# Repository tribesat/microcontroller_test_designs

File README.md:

# microcontroller_test_designs
Practice designing and manufacturing microcontroller boards

# License Information

The hardware is released under [Creative Commons Share-alike 3.0](http://creativecommons.org/licenses/by-sa/3.0/).  

## ATmega328P_QFP

These desgines are adapted from the [Sparkfun Arduino Pro Mini](https://github.com/sparkfun/Arduino_Pro_Mini_328)

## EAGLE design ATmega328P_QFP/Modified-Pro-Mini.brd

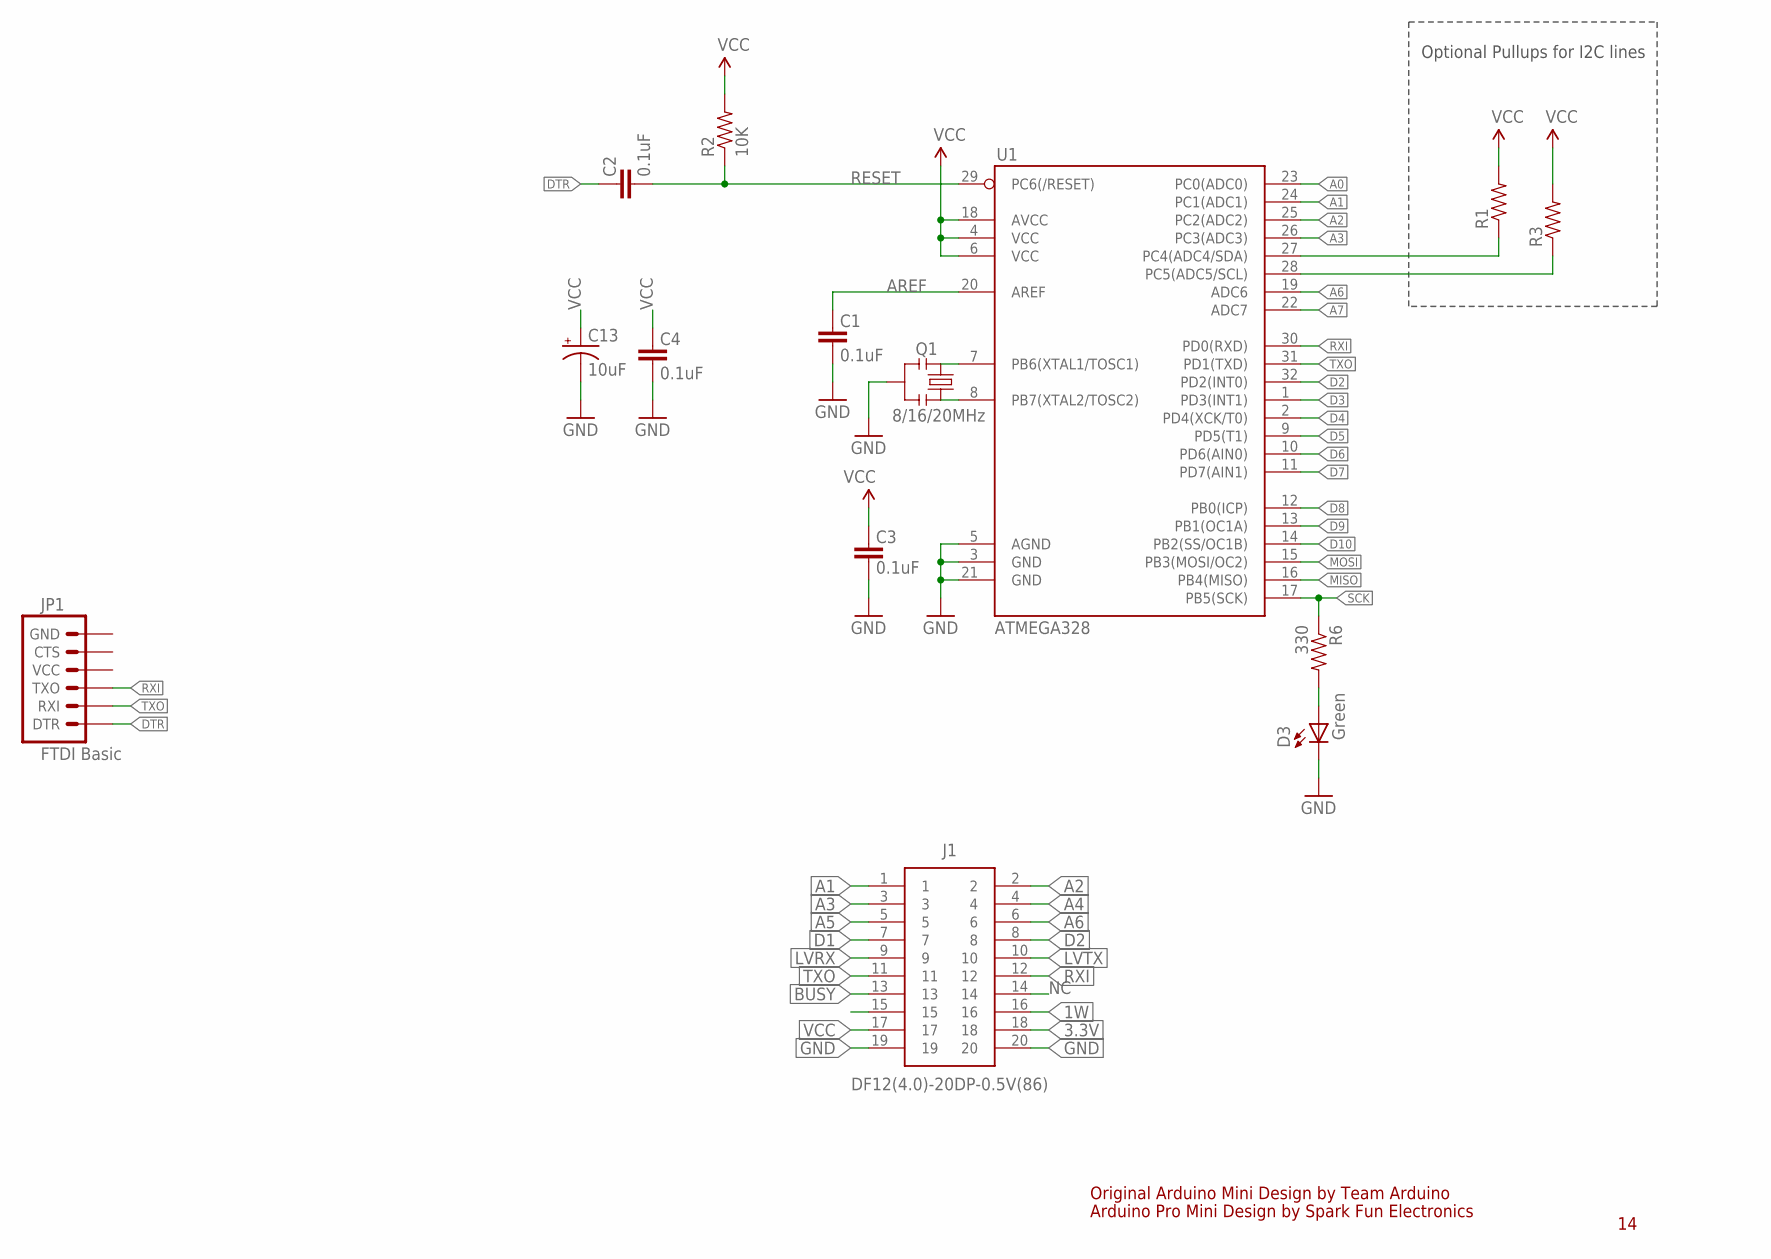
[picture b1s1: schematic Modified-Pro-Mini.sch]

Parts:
C1, C2, C3, C4: 0.1uF; 0603-CAP
C13: 10uF; EIA3216
D3: Green; 0603-LED-ALT1
J1: DF12(4.0)-20DP-0.5V(86); DF12(4.0)-20DP
JP1: FTDI Basic; 1X06
Q1: 8/16/20MHz; RESONATOR-SMD-1:1
R1, R3: RESISTOR0603-RES; 0603-RES
R2: 10K; 0603-RES
R6: 330; 0603-RES
U1: ATMEGA328; TQFP32-08

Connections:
1W: J1.16
3.3V: J1.18
A0: U1.23 (PC0(ADC0))
A1: J1.1, U1.24 (PC1(ADC1))
A2: J1.2, U1.25 (PC2(ADC2))
A3: J1.3, U1.26 (PC3(ADC3))
A4: J1.4, R1.1, U1.27 (PC4(ADC4/SDA))
A5: J1.5, R3.1, U1.28 (PC5(ADC5/SCL))
A6: J1.6, U1.19 (ADC6)
A7: U1.22 (ADC7)
AREF: C1.2, U1.20 (AREF)
BUSY: J1.13
D1: J1.7
D2: J1.8, U1.32 (PD2(INT0))
D3: U1.1 (PD3(INT1))
D4: U1.2 (PD4(XCK/T0))
D5: U1.9 (PD5(T1))
D6: U1.10 (PD6(AIN0))
D7: U1.11 (PD7(AIN1))
D8: U1.12 (PB0(ICP))
D9: U1.13 (PB1(OC1A))
D10: U1.14 (PB2(SS/OC1B))
DTR: C2.2, JP1.1 (DTR)
GND: C1.1, C3.1, C4.1, C13.C (-), D3.C, J1.19, J1.20, Q1.2, U1.3 (GND), U1.5 (AGND), U1.21 (GND)
LVRX: J1.9
LVTX: J1.10
MISO: U1.16 (PB4(MISO))
MOSI: U1.15 (PB3(MOSI/OC2))
unnamed: Q1.3, U1.8 (PB7(XTAL2/TOSC2))
unnamed: Q1.1, U1.7 (PB6(XTAL1/TOSC1))
unnamed: D3.A, R6.2
NC: J1.14
RESET: C2.1, R2.1, U1.29 (PC6(/RESET))
RXI: J1.12, JP1.3 (TXO), U1.30 (PD0(RXD))
SCK: R6.1, U1.17 (PB5(SCK))
TXO: J1.11, JP1.2 (RXI), U1.31 (PD1(TXD))
VCC: C3.2, C4.2, C13.A (+), J1.17, R1.2, R2.2, R3.2, U1.4 (VCC), U1.6 (VCC), U1.18 (AVCC)

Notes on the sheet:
Original Arduino Mini Design by Team Arduino
Arduino Pro Mini Design by Spark Fun Electronics
Optional Pullups for I2C lines

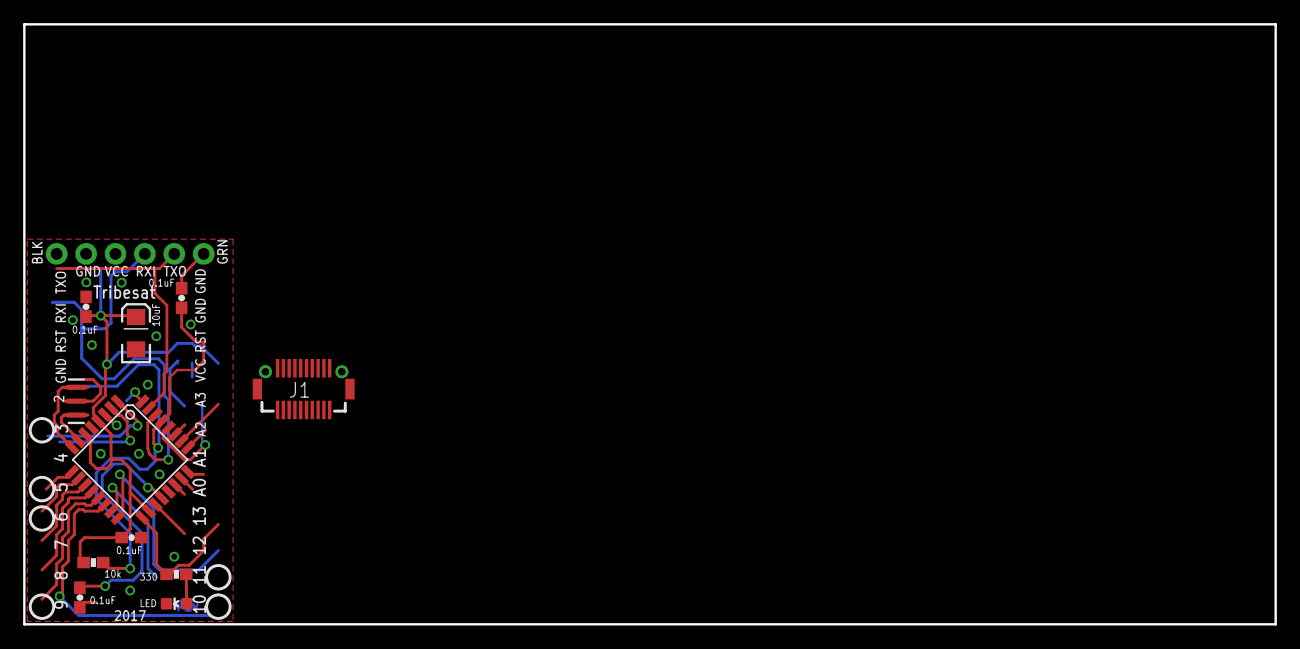
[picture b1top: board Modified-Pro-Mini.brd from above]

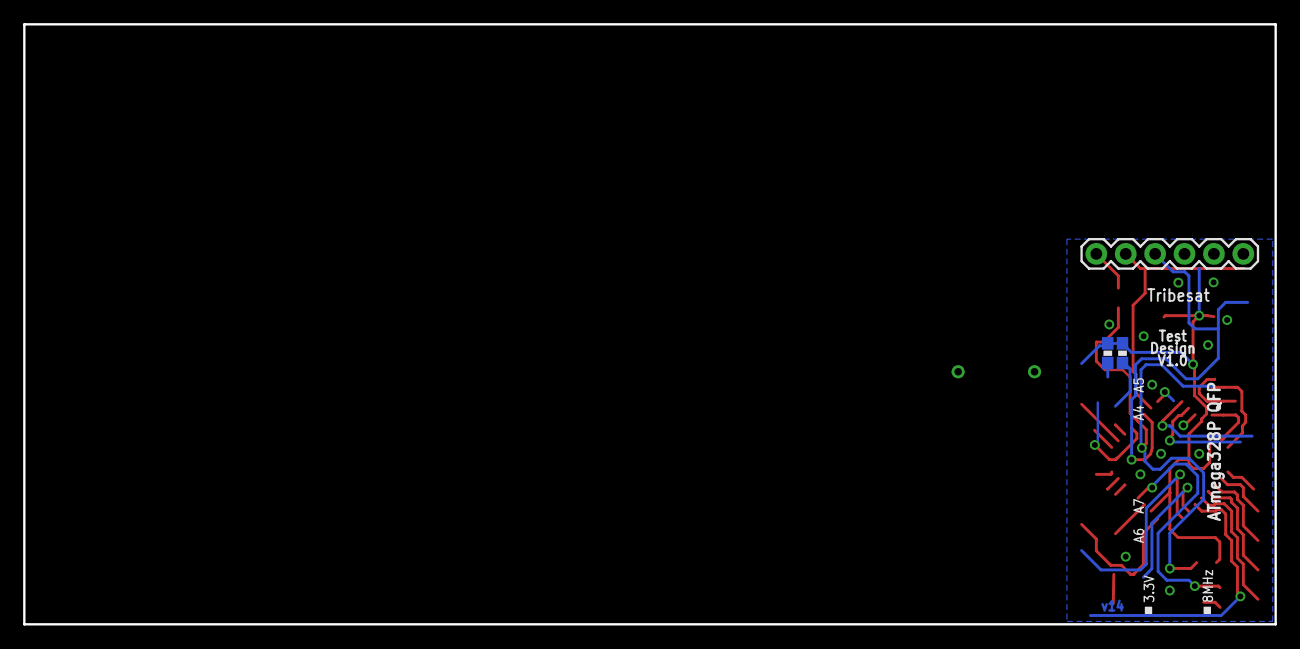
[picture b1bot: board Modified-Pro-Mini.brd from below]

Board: 2 copper layers, 108.1 x 51.8 mm, 14 parts (3 on the bottom side), 18 nets.

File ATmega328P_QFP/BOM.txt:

component/value, size, quanity, digikey part number
--------------------------------------------------------
ATmega328P, 32-TQFP, 1, ATMEGA328P-AURCT-ND
8MHz Resonator, 3-SMD, 1, 490-1195-1-ND
0.1uF Capacitor, 0603, 4, 311-1088-1-ND
10uF Polarized Capacitor, 1206, 1, 478-1654-1-ND
10k Resistor, 0603, 1, 311-10.0KHRCT-ND
330 Resistor, 0603, 1, 311-330HRCT-ND
Green LED, 0603, 1, 350-2035-1-ND

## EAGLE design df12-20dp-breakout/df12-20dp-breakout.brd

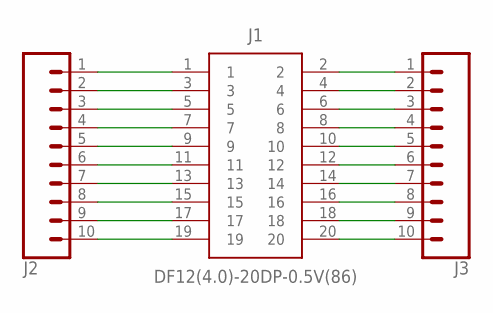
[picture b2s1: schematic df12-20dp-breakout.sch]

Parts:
J1: DF12(4.0)-20DP-0.5V(86); DF12(4.0)-20DP
J2, J3: CONN_10LOCK_LONGPADS; 1X10_LOCK_LONGPADS

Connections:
unnamed: J1.17, J2.9
unnamed: J1.15, J2.8
unnamed: J1.13, J2.7
unnamed: J1.11, J2.6
unnamed: J1.9, J2.5
unnamed: J1.7, J2.4
unnamed: J1.19, J2.10
unnamed: J1.5, J2.3
unnamed: J1.3, J2.2
unnamed: J1.1, J2.1
unnamed: J1.2, J3.1
unnamed: J1.4, J3.2
unnamed: J1.6, J3.3
unnamed: J1.8, J3.4
unnamed: J1.10, J3.5
unnamed: J1.12, J3.6
unnamed: J1.14, J3.7
unnamed: J1.16, J3.8
unnamed: J1.18, J3.9
unnamed: J1.20, J3.10

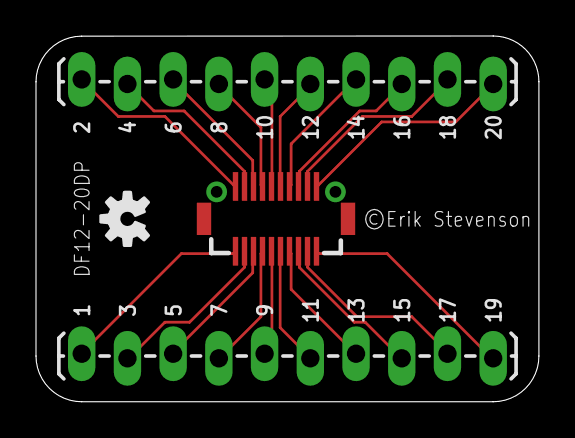
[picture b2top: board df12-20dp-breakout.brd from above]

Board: 2 copper layers, 27.9 x 20.3 mm, 4 parts (0 on the bottom side), 20 nets.

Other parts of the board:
U$1: OSHW-LOGO-S

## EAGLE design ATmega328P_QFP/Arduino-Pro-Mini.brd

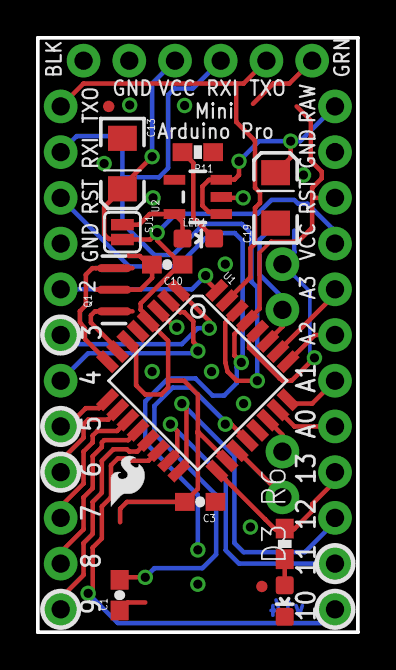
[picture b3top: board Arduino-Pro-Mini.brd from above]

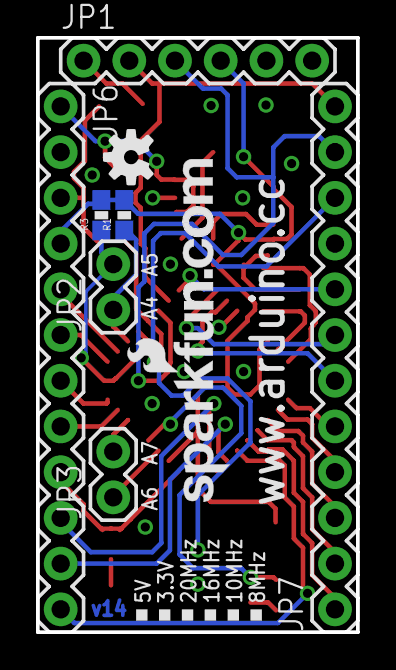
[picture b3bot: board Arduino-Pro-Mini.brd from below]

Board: 2 copper layers, 17.8 x 33.0 mm, 25 parts (9 on the bottom side), 32 nets.

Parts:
C1, C3, C10: 0.1uF; 0603-CAP
C13, C19: 10uF; EIA3216
D3: Green; 0603-LED-ALT1
JP1: FTDI Basic; 1X06
JP2, JP3: 1X02
JP5, JP8: FIDUCIALUFIDUCIAL; MICRO-FIDUCIAL
JP6, JP7: 1X12
LED1: Red; 0603-LED-ALT1
Q1: 8/16/20MHz; RESONATOR-SMD-1:1
R1, R3: 0603-RES
R6: 330; 0603-RES
R11: 10K; 0603-RES
SJ1: SJ_2S
U1: ATMEGA328; TQFP32-08
U2: MIC5205; SOT23-5
U$1: LOGO-SFESK; SFE-LOGO-FLAME
U$3: OSHW-LOGOS; OSHW-LOGO-S
U$11: LOGO-SFENEW; SFE-NEW-WEBLOGO

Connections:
A0: JP6.8, U1.23
A1: JP6.7, U1.24
A2: JP6.6, U1.25
A3: JP6.5, U1.26
A4: JP2.1, R1.1, U1.27
A5: JP2.2, R3.1, U1.28
A6: JP3.1, U1.19
A7: JP3.2, U1.22
AREF: C1.2, U1.20
D2: JP7.8, U1.32
D3: JP7.7, U1.1
D4: JP7.6, U1.2
D5: JP7.5, U1.9
D6: JP7.4, U1.10
D7: JP7.3, U1.11
D8: JP7.2, U1.12
D9: JP7.1, U1.13
D10: JP6.12, U1.14
GND: C1.1, C3.1, C10.2, C13.C, C19.C, D3.C, JP1.5, JP1.6, JP6.2, JP7.9, Q1.2, R11.1, U1.3, U1.5, U1.21, U2.2
MISO: JP6.10, U1.16
MOSI: JP6.11, U1.15
unnamed: Q1.3, U1.8
unnamed: Q1.1, U1.7
unnamed: LED1.A, SJ1.1, U2.5
unnamed: LED1.C, R11.2
unnamed: D3.A, R6.2
RAW: C19.A, JP6.1, U2.1, U2.3
RESET: JP6.3, JP7.10, U1.29
RXI: JP1.3, JP7.11, U1.30
SCK: JP6.9, R6.1, U1.17
TXO: JP1.2, JP7.12, U1.31
VCC: C3.2, C10.1, C13.A, JP1.4, JP6.4, R1.2, R3.2, SJ1.2, U1.4, U1.6, U1.18

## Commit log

2017-09-18 added git ignore
2017-09-18 add licens info
    added linces info for the 328p QFP
2017-09-18 added lightly modfied arduino pro mini
    this is the 328p QFP reference desgine
    removed physical reset button from the pro mini desgines
2017-09-18 file rename
2017-09-18 updated silk
2017-09-18 removed power regulator
2017-09-19 rerouted wires left by removed compoents
2017-09-19 changed raw pin to gnd
2017-09-19 bumbed out all sides by 0.01in
    got board to pass OSH park DRC
2017-09-26 updated silk with board and part info
2017-09-26 added decoupling cap
2017-09-29 palced decoupling cap
2017-09-29 created BOM, missing digikey part numbers
2017-09-29 Filled in DigiKey part numbers
2017-09-29 Change back to txt file
2017-09-29 fixed DRC errors
2017-09-30 Fix typo in bPlace layer
2017-09-30 Filled in DigiKey part numbers (#3)
    * Filled in DigiKey part numbers
2017-09-30 Remove fiducials
2017-09-30 Cleared the tNames layer
2017-09-30 Slight adjustments to prevent text from overlapping copper
2017-09-30 got rid of kink in TXO line
    moved via slightly
2017-09-30 bottom silk tweak
2017-09-30 Prepare silkscreen layers for OSH Park printing (#4)
    * Fix typo in bPlace layer
    * Remove fiducials
    * Cleared the tNames layer
    * Slight adjustments to prevent text from overlapping copper
    * got rid of kink in TXO line
    * moved via slightly
2017-10-02 added LED to 328P QFP BOM
2017-10-02 straigtened VCC line
2017-10-04 updated BOM part number
    0.1uF cap was 0603 metric, our measurements are in imperial
2017-10-28 created assembly instructions
2017-10-29 added documentation
2017-11-20 added pictures of process
2018-01-31 Create df12-20dp breakout board design
2018-01-31 Align pins to multiple of .1 for breadboard
2018-01-31 Add silkscreen
2018-01-31 Fix typo
2018-01-31 Add df12-20dp footprint library file
2018-01-31 Add df12-20dp footprint library file (#7)
2018-01-31 Df12 20dp breakout (#8)
    * Create df12-20dp breakout board design
    * Align pins to multiple of .1 for breadboard
    * Add silkscreen
    * Fix typo
    * Add df12-20dp footprint library file (#7)
2018-02-06 New board design: - larger footprint by the ICD requirements (no holes) - removed headers - added DF12 connector footprint

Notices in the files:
df12-20dp-breakout/df12-20dp-breakout.brd:
©Erik Stevenson
parts and their libraries:
SparkFun-Passives: Licensing: CC v3.0 Share-Alike You are welcome to use this library for commercial purposes.
SparkFun-Connectors: Licensing: Creative Commons ShareAlike 4.0 International - https://creativecommons.org/licenses/by-sa/4.0
